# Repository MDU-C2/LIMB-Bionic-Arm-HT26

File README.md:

# AURORA

AURORA is a student project at [Mälardalen University](https://www.mdu.se/)
with the aim of developing a bionic arm for the rehabilitation of stroke
survivors. The project continues the work started in LIMB. This repository
contains the sensor firmware, recording tools, arm simulation and movement
training code.

## Platforms used

The current setup uses an ESP32-C3-Zero to read EMG and two LSM6DSO32 IMUs,
an OAK-D camera to track arm movement, and a PC to run the app and PyBullet
simulation. The ESP32 sends sensor data over Bluetooth Low Energy. The camera
connects to the PC by USB.

## Running the program

On Windows, run `Setup.bat` for the first setup, then use `Start.bat` to open
the app offline. Setup installs all app packages, checks the pose models and builds
firmware; it needs internet. See the
[setup notes](scripts/README.md) for direct launching and the macOS/Linux scripts.

Follow the [workflow guide](docs/workflow-guide.md) to connect and inspect,
prepare/calibrate, record or control, then review, process and export.
Advanced Tools contains optional training, DMP/manual joints, diagnostics and firmware.
See [architecture](docs/architecture.md) for code ownership and development conventions.

## Before recording

For the Grove EMG Detector cable with white wires and red, black and white snap heads:

| Lead | Electrode placement for grip |
| --- | --- |
| Red | Reference on a bony area near the elbow, away from the measured muscle. |
| Black | Palm-facing forearm, over the muscle that firms when making a fist. |
| White | Same muscle, a few centimetres towards the wrist from the black electrode. |

Keep black and white in line along the muscle without overlapping the pads.
Use clean, dry skin. These colours apply to this cable; see
[Seeed's placement and cable diagrams](https://wiki.seeedstudio.com/Grove-EMG_Detector/#hardware-installation).
Use battery power and BLE with USB and chargers disconnected while wearing electrodes.

In **Record**, connect camera + BLE and run **Calibrate subject** before the first
trial. This includes IMU zeroing, mounting movements and EMG rest/grip calibration.
See the [recording guide](docs/recording-guide.md#before-the-first-trial) for the
still pose and when to repeat calibration.

## Structure of repository

The main folders are:

- [`scripts/`](scripts/README.md): setup and sensor checks.
- [`src/aurora/gui/`](src/aurora/gui/README.md): the desktop app.
- [`src/aurora/sensors/`](src/aurora/sensors/README.md): sensor input, camera tracking and fusion.
- [`src/aurora/recording/`](src/aurora/recording/README.md): sensor and camera recording, grip trials and EMG processing.
- [`src/aurora/simulation/`](src/aurora/simulation/README.md): the arm simulation and playback.
- [`src/aurora/ml/`](src/aurora/ml/README.md): movement profiles and EMG classifiers.
- [`firmware/`](firmware/README.md): programs running on the ESP32-C3.
- [`data/`](data/README.md): inherited movement recordings, kept separately.
- [`docs/`](docs/README.md): setup, recording and simulation guides.
- [`tests/`](tests/README.md): software checks.

Bundled models are in `artifacts/models/`. New recordings, training runs and
generated files go in `outputs/`, which is ignored by Git.

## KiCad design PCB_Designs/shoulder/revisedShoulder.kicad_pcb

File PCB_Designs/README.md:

# PCB Designs – AURORA HT26

## Overview

This directory contains the PCB designs developed and used in the AURORA project. The boards are designed to support the robotic arm's motor control, sensor acquisition, and communication systems.

Each PCB project contains the necessary design and manufacturing files, including:

- **Schematic** – Electrical circuit design.
- **PCB Layout** – Physical component placement and routing.
- **Footprint Library** – Custom component footprints.
- **BOM (Bill of Materials)** – List of required components.
- **Gerber & Drill Files** – Files required for PCB manufacturing.

The designs are developed using **KiCad 10** and **National Instrument Multisim/Ultiboard**.

---

## PCB Modules

### 1. Biceps_Module

This PCB controls the motors responsible for movement of the biceps/lower arm using X and Y control inputs.
The module communicates with the other robotic arm controllers through the CAN bus.
- **CAN Node:** 2 of 4
- **CAN Position:** Between Shoulder (Node 1) and Hand_Motor (Node 3)
- **CAN Termination:** Not required

### 2. CAN_Transceiver

This PCB is a custom CAN transceiver board designed to enable CAN communication between the Jetson AGX Orin and the robotic arm's motor controllers.
The design is based on the [Waveshare SN65HVD230 CAN Board](https://www.waveshare.com/sn65hvd230-can-board.htm).
To reduce dependency on external component delivery times, the project group developed a custom version that could be manufactured and assembled in-house.
The same PCB design can be used throughout the CAN network.

**Important – CAN Bus Termination**
A 120 Ω termination resistor must only be installed at the two physical ends of the CAN bus.
| CAN Transceiver Location | 120 Ω Resistor |
|---|---|
| Jetson AGX Orin → Shoulder (bus start) | Installed |
| Shoulder | Not Installed |
| Biceps_Module | Not installed |
| Hand_Motor | Not installed |
| Hand_Pressure (bus end) | Installed |

Incorrect termination may lead to signal reflections, communication errors, and unstable CAN operation.

### 3. Hand_Motor

This PCB controls the motors responsible for hand movement.
It receives control commands through the CAN bus and operates as the third node in the robotic arm's communication network.
- **CAN Node:** 3 of 4
- **CAN Position:** Between Biceps_Module and Hand_Pressure
- **CAN Termination:** Not required

### 4. Hand_Pressure

This PCB is responsible for acquiring pressure measurements from the robotic hand during object grasping.
The collected sensor data can be used to monitor contact pressure and support grip control.
- **CAN Node:** 4 of 4
- **CAN Position:** Final node on the CAN bus
- **CAN Termination:** Required (120 Ω)
The CAN transceiver connected to this module must have its termination resistor installed.

### 5. Human_Sensor

This PCB is designed for the acquisition, amplification, and filtering of electromyography (EMG) signals.
The analog signal-conditioning circuit amplifies the small electrical signals generated by muscle activity and filters unwanted noise before the signals are acquired by the microcontroller.

The intended output characteristics are:
- **Resting state: Approximately 1.5 V DC output.
- **Signal noise: Low peak-to-peak voltage during rest.
- **Muscle activation: Changes in the output signal corresponding to measured muscle activity.

The PCB also provides mounting positions for:
- **ESP32-C3 – Microcontroller for data acquisition and communication.
- **IMU – Inertial Measurement Unit for motion sensing.

The Human_Sensor PCB is part of the user-worn sensing system and is separate from the robotic arm's CAN motor-controller network.

CAN Bus Architecture
The robotic arm uses a shared CAN bus connecting the Jetson AGX Orin to four ESP32-based control nodes.

Jetson AGX Orin
       |
  CAN Transceiver
   [120 Ω ON]
       |
       |
 Shoulder Module
     Node 1
       |
       |
 Biceps_Module
     Node 2
       |
       |
   Hand_Motor
     Node 3
       |
       |
  Hand_Pressure
     Node 4
   [120 Ω ON]

Note: The termination resistors must be located at the two physical endpoints of the CAN bus. The diagram represents the intended bus topology; exact transceiver placement depends on the final wiring arrangement.

Notes
The custom CAN transceiver PCB is designed for reuse across multiple robotic arm modules.
CAN termination must be configured according to the physical bus topology.
Custom KiCad footprints are stored in the corresponding project libraries to simplify project sharing.
PCB designs should be verified before manufacturing or assembly.

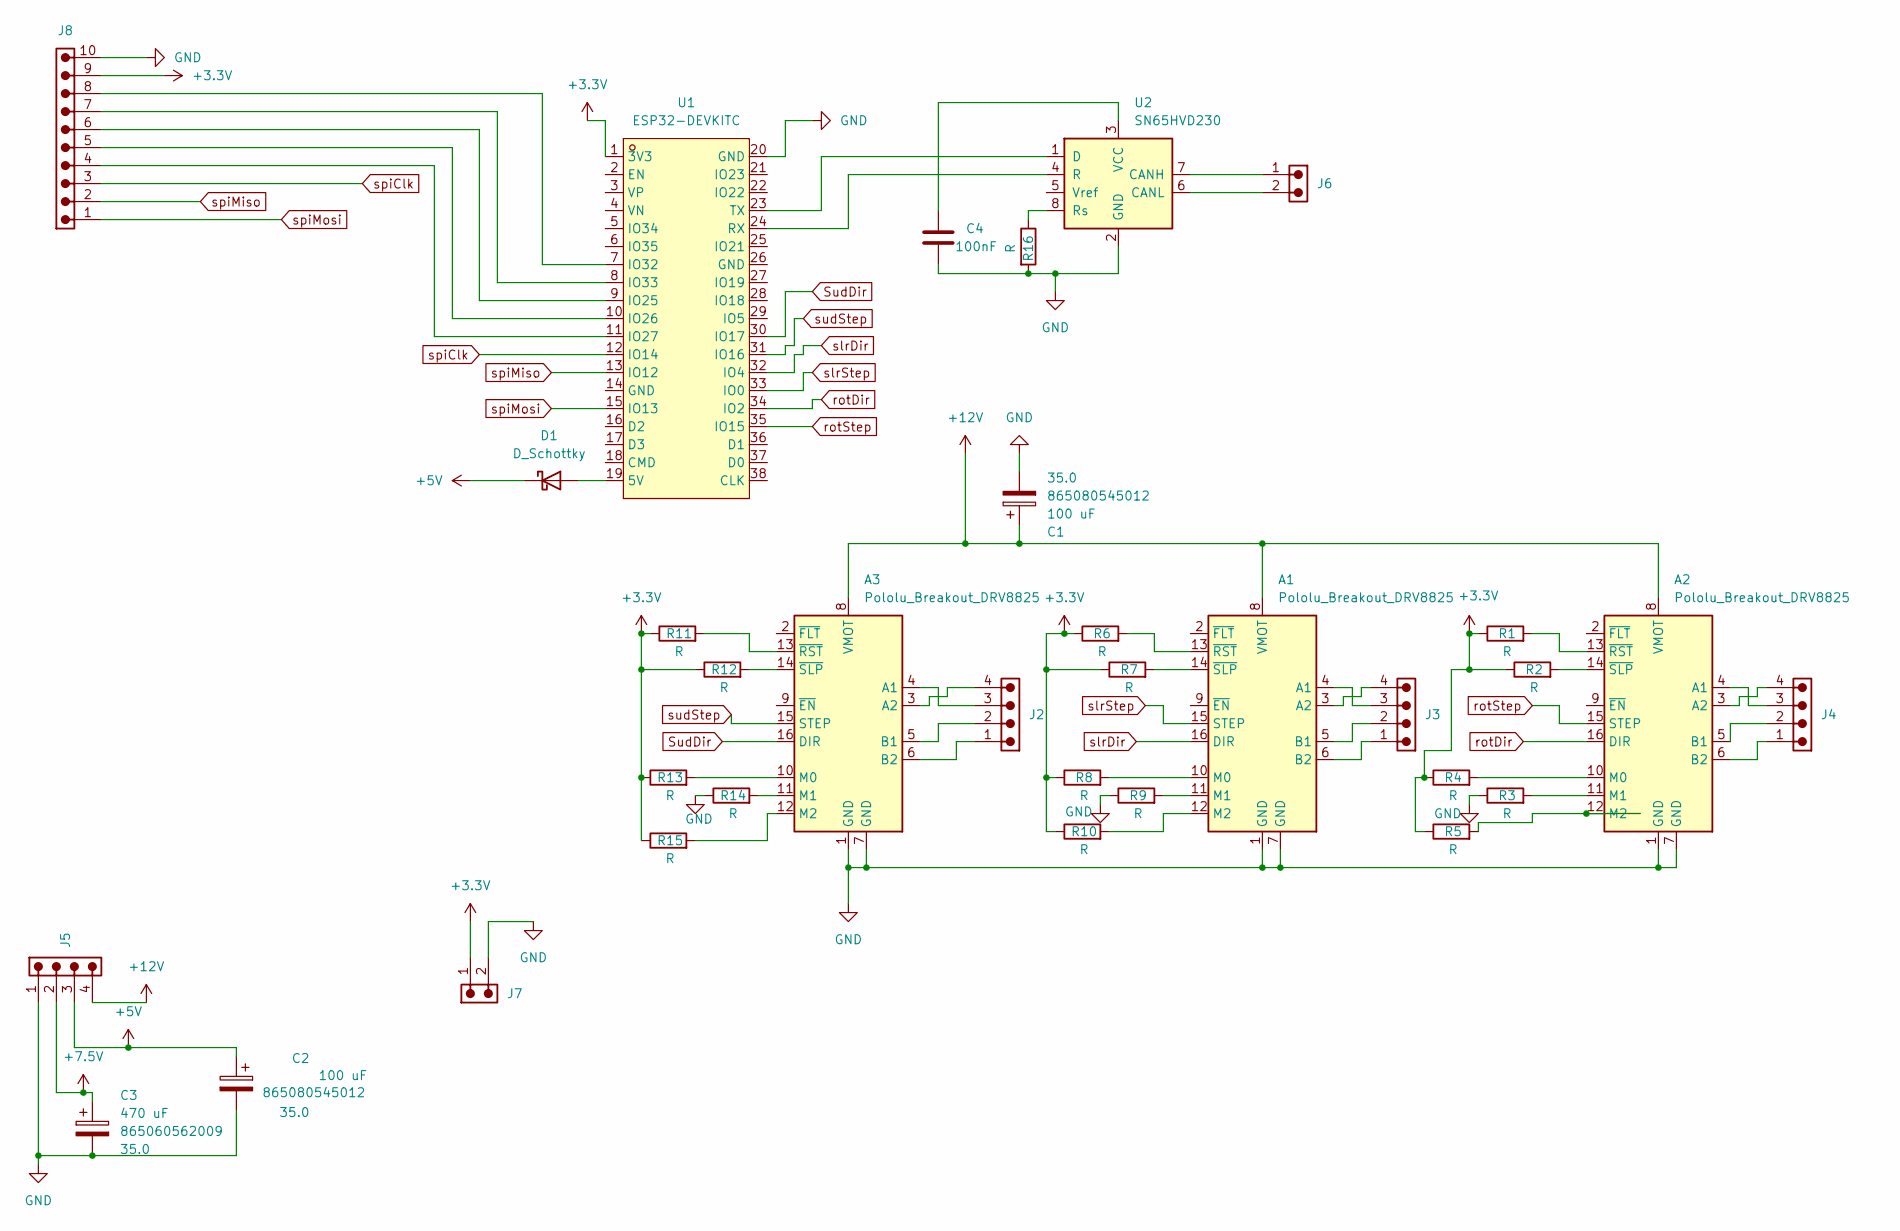
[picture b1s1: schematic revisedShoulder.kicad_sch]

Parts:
A1, A2, A3: Pololu_Breakout_DRV8825; Pololu_Breakout-16_15.2x20.3mm
C1, C2: 100 uF; CP_Wurth_WCAP-ASLI-D6.3L7.7; Voltage 35.0; Part Number 865080545012
C3: 470 uF; CP_Wurth_WCAP-ASLL-D12.5L14; Voltage 35.0; Part Number 865060562009
C4: 100nF; C_0805_2012Metric_Pad1.18x1.45mm_HandSolder
D1: D_Schottky; D_SMA_Handsoldering
J2, J3, J4: 61900411121; J_Wurth_WR-WTB_61900411121; Working Voltage (V (AC)) 250
J5: 68800411622; J_Wurth_WR-WTB_68800411622; Working Voltage (V (AC)) 250
J6, J7: 68800211622; J_Wurth_WR-WTB_68800211622; Working Voltage (V (AC)) 250
J8: 68801011622; J_Wurth_WR-WTB_68801011622; Working Voltage (V (AC)) 250
R1, R2, R3, R4, R5, R6, R7, R8, R9, R10, R11, R12, R13, R14, R15, R16: R; R_0805_2012Metric_Pad1.20x1.40mm_HandSolder
U1: ESP32-DEVKITC; BULETM-SMD_ESP32-DEVKITC; MPN ESP32-DevKitC; LCSC Part C571180
U2: SN65HVD230; SOIC-8_3.9x4.9mm_P1.27mm

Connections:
+3.3V: J7.1, J8.9, R1.1, R2.1, R4.1, R5.1, R6.1, R7.1, R8.1, R10.1, R11.1, R12.1, R13.1, R15.1, U1.1 (3V3)
+5V: C2.1, D1.1 (K), J5.3
+7.5V: C3.1, J5.2
+12V: A1.8 (VMOT), A2.8 (VMOT), A3.8 (VMOT), C1.1, J5.4
GND: A1.1 (GND), A1.7 (GND), A2.1 (GND), A2.7 (GND), A3.1 (GND), A3.7 (GND), C1.2, C2.2, C3.2, C4.2, J5.1, J7.2, J8.10, R3.1, R9.1, R14.1, R16.2, U1.20 (GND), U2.2 (GND)
unnamed: A1.4 (A1), J3.3
unnamed: A1.3 (A2), J3.4
unnamed: A1.5 (B1), J3.2
unnamed: A1.6 (B2), J3.1
unnamed: A1.10 (M0), R8.2
unnamed: A1.11 (M1), R9.2
unnamed: A1.12 (M2), R10.2
unnamed: A1.13 (~RST), R6.2
unnamed: A1.14 (~SLP), R7.2
unnamed: A2.4 (A1), J4.3
unnamed: A2.3 (A2), J4.4
unnamed: A2.5 (B1), J4.2
unnamed: A2.6 (B2), J4.1
unnamed: A2.10 (M0), R4.2
unnamed: A2.11 (M1), R3.2
unnamed: A2.12 (M2), R5.2
unnamed: A2.13 (~RST), R1.2
unnamed: A2.14 (~SLP), R2.2
unnamed: A3.4 (A1), J2.3
unnamed: A3.3 (A2), J2.4
unnamed: A3.5 (B1), J2.2
unnamed: A3.6 (B2), J2.1
unnamed: A3.10 (M0), R13.2
unnamed: A3.11 (M1), R14.2
unnamed: A3.12 (M2), R15.2
unnamed: A3.13 (~RST), R11.2
unnamed: A3.14 (~SLP), R12.2
unnamed: D1.2 (A), U1.19 (5V)
unnamed: J8.6, U1.9 (IO25)
unnamed: J8.5, U1.10 (IO26)
unnamed: J8.4, U1.11 (IO27)
unnamed: J8.8, U1.7 (IO32)
unnamed: J8.7, U1.8 (IO33)
unnamed: U1.24 (RX), U2.4 (R)
unnamed: U1.23 (TX), U2.1 (D)
unnamed: J6.1, U2.7 (CANH)
unnamed: J6.2, U2.6 (CANL)
unnamed: R16.1, U2.8 (Rs)
unnamed: C4.1, U2.3 (VCC)
SudDir: A3.16 (DIR), U1.30 (IO17)
rotDir: A2.16 (DIR), U1.34 (IO2)
rotStep: A2.15 (STEP), U1.35 (IO15)
slrDir: A1.16 (DIR), U1.32 (IO4)
slrStep: A1.15 (STEP), U1.33 (IO0)
spiClk: J8.3, U1.12 (IO14)
spiMiso: J8.2, U1.13 (IO12)
spiMosi: J8.1, U1.15 (IO13)
sudStep: A3.15 (STEP), U1.31 (IO16)

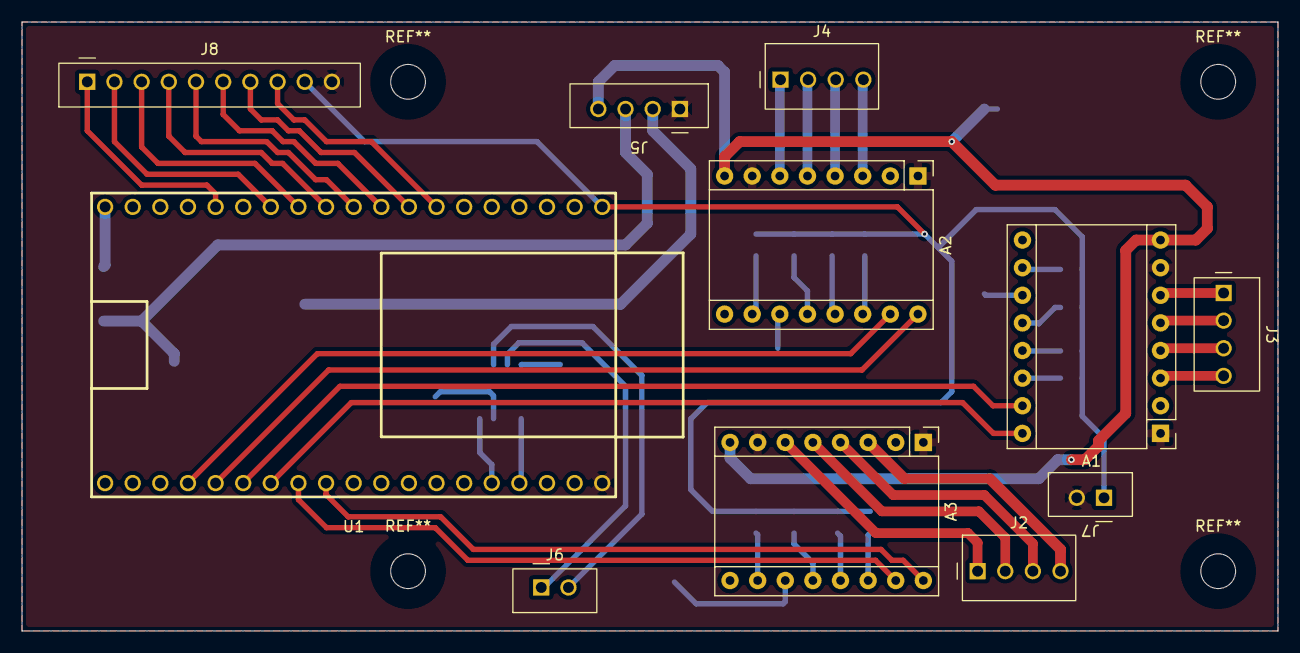
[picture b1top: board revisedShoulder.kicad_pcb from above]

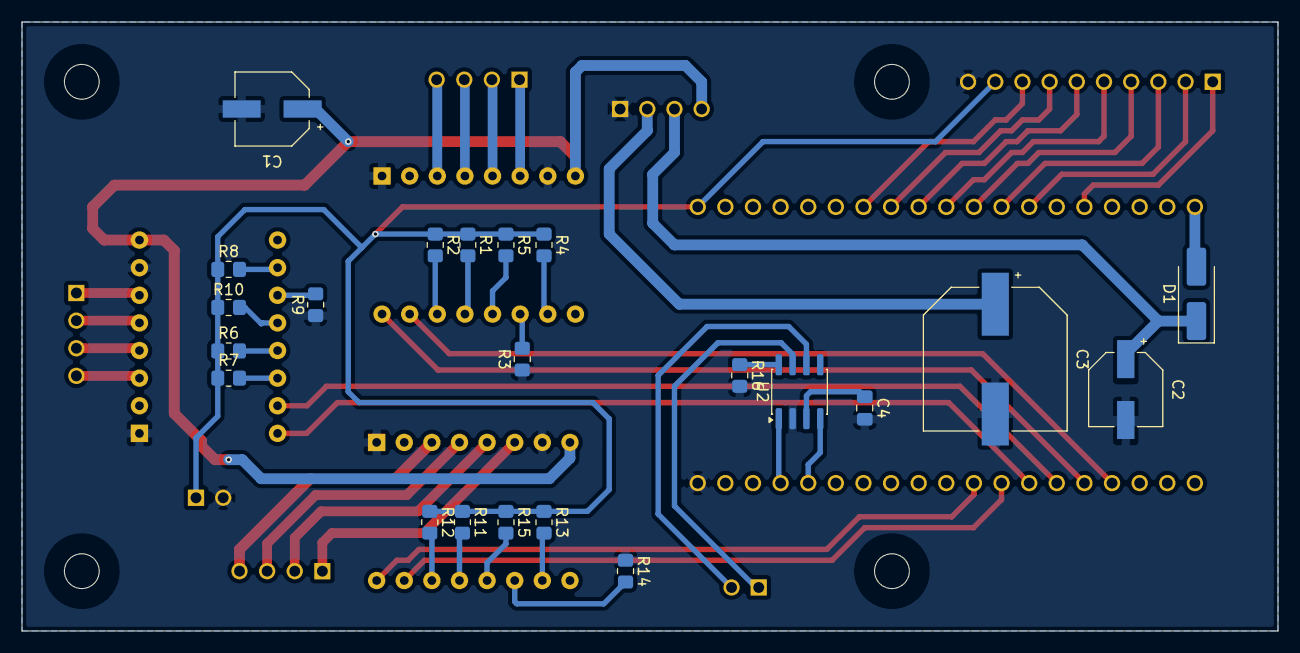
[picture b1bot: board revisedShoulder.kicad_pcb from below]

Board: 2 copper layers, 115.5 x 56.0 mm, 33 parts (22 on the bottom side), 53 nets.

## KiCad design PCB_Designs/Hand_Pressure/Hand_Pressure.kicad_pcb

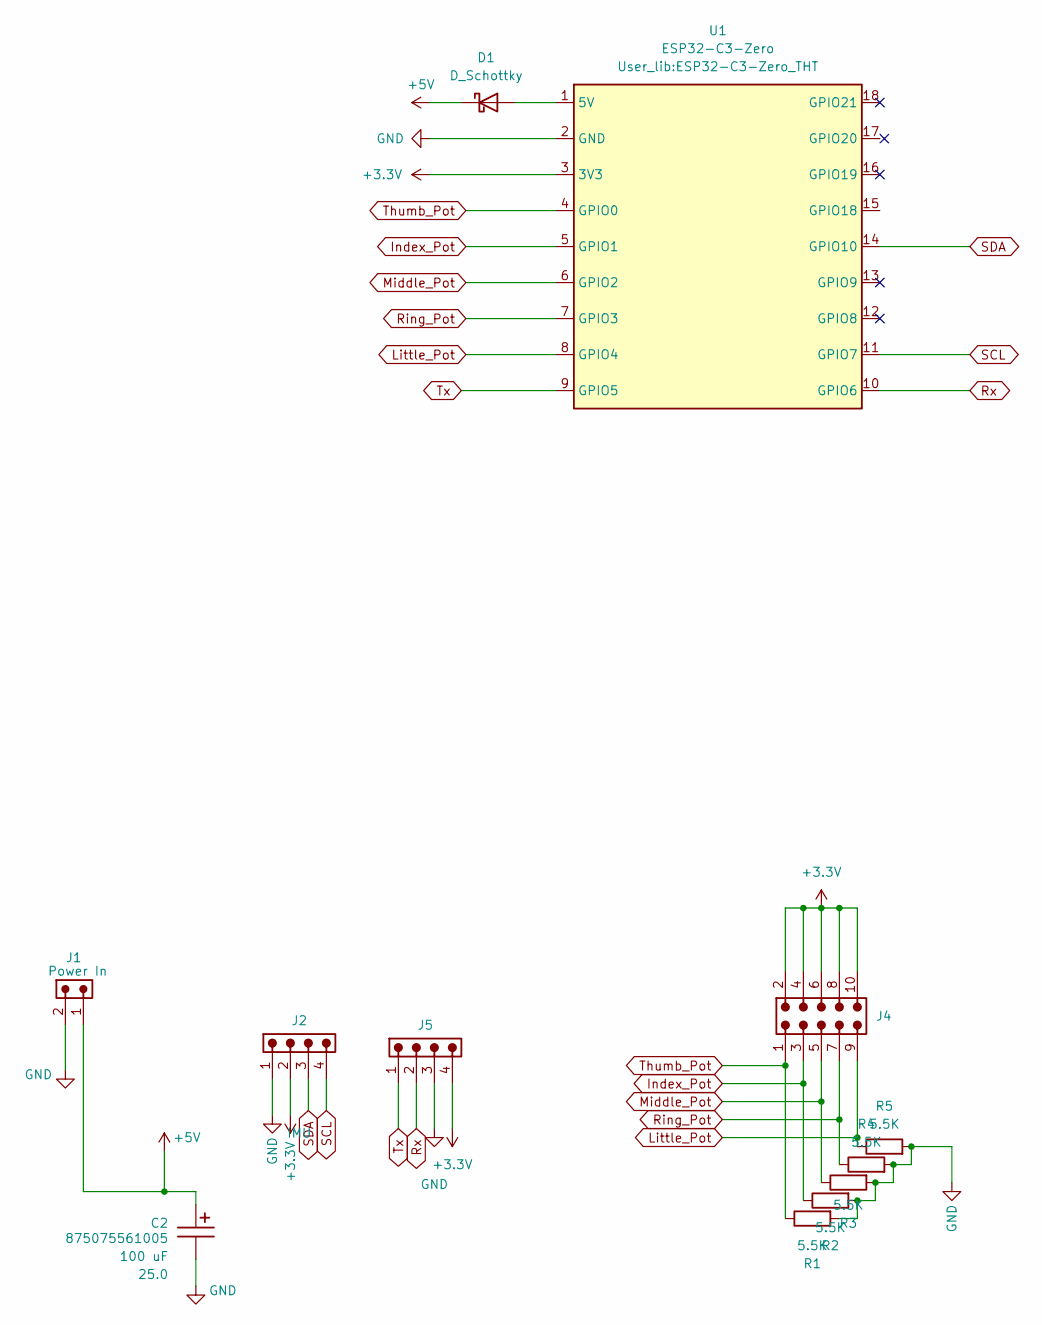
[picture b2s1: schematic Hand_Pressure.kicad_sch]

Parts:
C2: 100 uF; CP_Wurth_WCAP-ASLL-D6.3L5.5; Voltage 25.0; Part Number 875075561005
D1: D_Schottky; D_SMA
J1: Power In; J_Wurth_WR-NPC2_626002110201; Part Number 626002110201
J2: IMU; J_Wurth_WR-WTB_68800411622; Working Voltage (V (AC)) 250
J4: 61301021121; J_Wurth_WR-PHD_61301021121
J5: IMU; J_Wurth_WR-PHD_613004143121; Working Voltage (V (AC)) 250
R1, R2, R3, R4, R5: 5.5K; R_0805_2012Metric
U1: ESP32-C3-Zero; ESP32-C3-Zero_THT

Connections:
+3.3V: J2.2, J4.2, J4.4, J4.6, J4.8, J4.10, J5.4, U1.3 (3V3)
+5V: C2.1, D1.1 (K), J1.1
GND: C2.2, J1.2, J2.1, J5.3, R1.2, R2.2, R3.2, R4.2, R5.2, U1.2 (GND)
Index_Pot: J4.3, R2.1, U1.5 (GPIO1)
Little_Pot: J4.9, R5.1, U1.8 (GPIO4)
Middle_Pot: J4.5, R3.1, U1.6 (GPIO2)
unnamed: D1.2 (A), U1.1 (5V)
Ring_Pot: J4.7, R4.1, U1.7 (GPIO3)
Rx: J5.2, U1.10 (GPIO6)
SCL: J2.4, U1.11 (GPIO7)
SDA: J2.3, U1.14 (GPIO10)
Thumb_Pot: J4.1, R1.1, U1.4 (GPIO0)
Tx: J5.1, U1.9 (GPIO5)

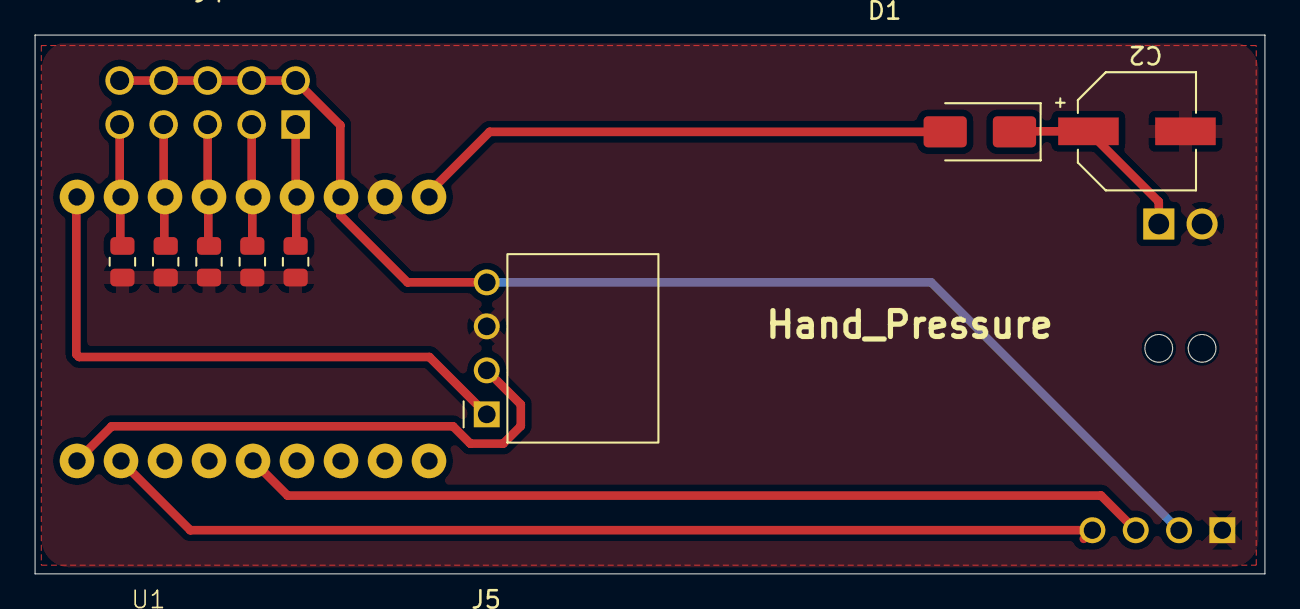
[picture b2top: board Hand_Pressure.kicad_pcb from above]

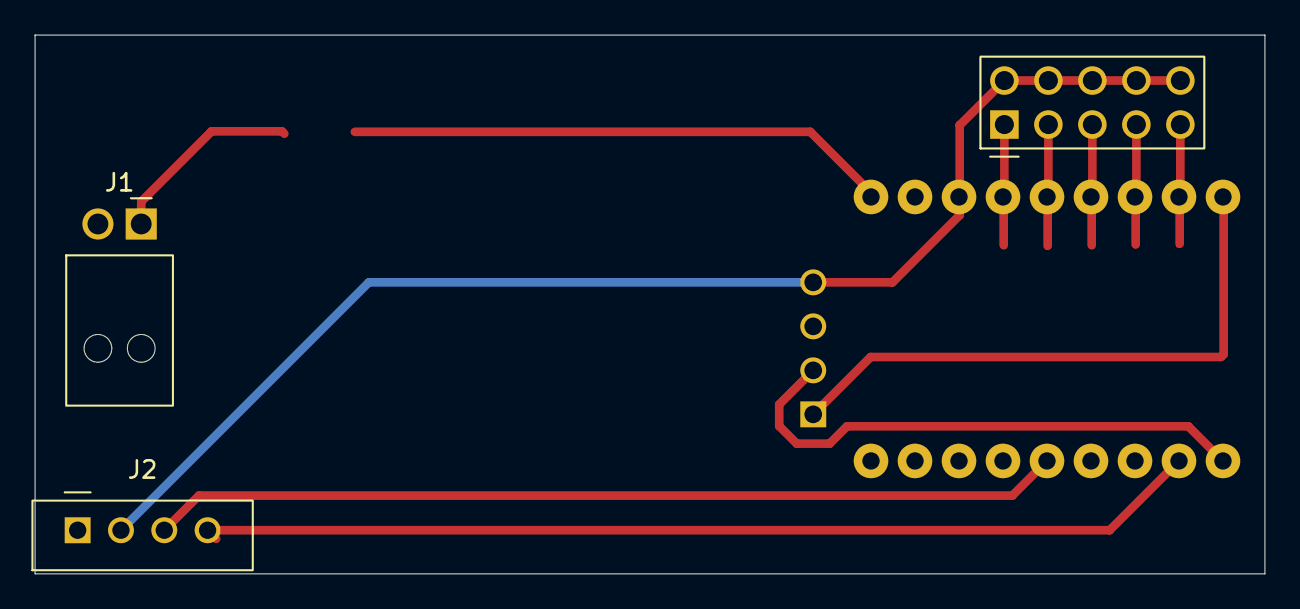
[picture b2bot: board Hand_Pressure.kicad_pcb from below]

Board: 2 copper layers, 71.0 x 31.1 mm, 12 parts (3 on the bottom side), 13 nets.

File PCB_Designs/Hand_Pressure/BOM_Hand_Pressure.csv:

Reference;Qty;Value;Footprint;Datasheet
C2;1;100 uF;Capacitor_SMD_Wurth:CP_Wurth_WCAP-ASLL-D6.3L5.5;https://www.we-online.com/catalog/datasheet/875075561005.pdf?ki
D1;1;D_Schottky;Diode_SMD:D_SMA;https://docs.rs-online.com/28a6/0900766b80de2cd0.pdf
J1;1;Power In;User_lib:J_Wurth_WR-NPC2_626002110201;https://www.we-online.com/catalog/datasheet/626002110201.pdf?ki
J2;1;IMU;User_lib:J_Wurth_WR-WTB_68800411622;https://www.we-online.com/en/components/products/datasheet/6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
J4;1;61301021121;User_lib:J_Wurth_WR-PHD_61301021121;https://www.we-online.com/en/components/products/datasheet/6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
J5;1;IMU;Connector_THT_Wurth:J_Wurth_WR-PHD_613004143121;https://www.we-online.com/components/products/datasheet/6130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
R1,R2,R3,R4,R5;5;5.5K;Resistor_SMD:R_0805_2012Metric;
U1;1;ESP32-C3-Zero;User_lib:ESP32-C3-Zero_THT;https://www.waveshare.com/wiki/ESP32-C3-Zero#Resource
U1;2;ESP32 Connector;9-pin Connectors for ESP32-C3 ;https://www.we-online.com/en/components/products/BTB_WR_PHD_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

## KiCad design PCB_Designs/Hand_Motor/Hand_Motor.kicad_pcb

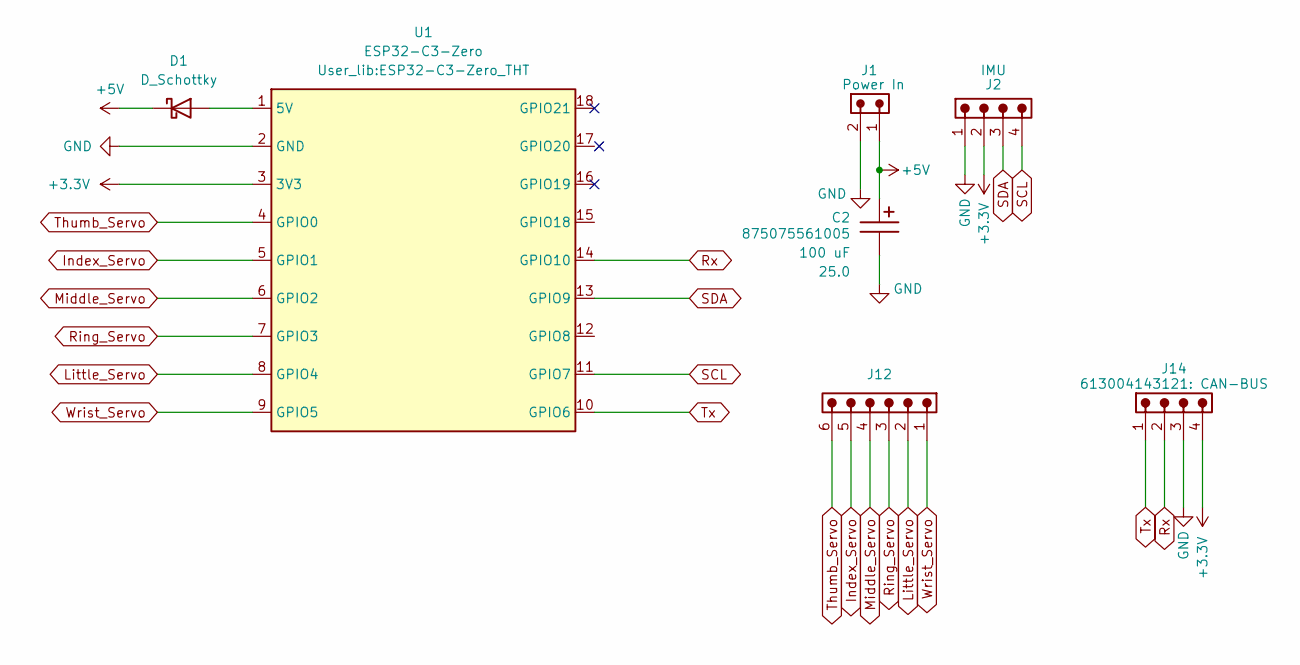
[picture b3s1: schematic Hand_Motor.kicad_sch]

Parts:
C2: 100 uF; CP_Wurth_WCAP-ASLL-D6.3L5.5; Voltage 25.0; Part Number 875075561005
D1: D_Schottky; D_SMA
J1: Power In; J_Wurth_WR-NPC2_626002110201; Part Number 626002110201
J2: IMU; J_Wurth_WR-WTB_68800411622; Working Voltage (V (AC)) 250
J12: 68800611722; J_Wurth_WR-WTB_68800611722; Working Voltage (V (AC)) 250
J14: 613004143121: CAN-BUS; PinHeader_1x04_P2.54mm_Vertical; Working Voltage (V (AC)) 250
U1: ESP32-C3-Zero; ESP32-C3-Zero_THT

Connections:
+3.3V: J2.2, J14.4, U1.3 (3V3); also elsewhere on the board
+5V: C2.1, D1.1 (K), J1.1
GND: C2.2, J1.2, J2.1, J14.3, U1.2 (GND); also elsewhere on the board
Index_Servo: J12.5, U1.5 (GPIO1)
Little_Servo: J12.2, U1.8 (GPIO4)
Middle_Servo: J12.4, U1.6 (GPIO2)
unnamed: D1.2 (A), U1.1 (5V)
Ring_Servo: J12.3, U1.7 (GPIO3)
Rx: J14.2, U1.14 (GPIO10)
SCL: J2.4, U1.11 (GPIO7)
SDA: J2.3, U1.13 (GPIO9)
Thumb_Servo: J12.6, U1.4 (GPIO0)
Tx: J14.1, U1.10 (GPIO6)
Wrist_Servo: J12.1, U1.9 (GPIO5)

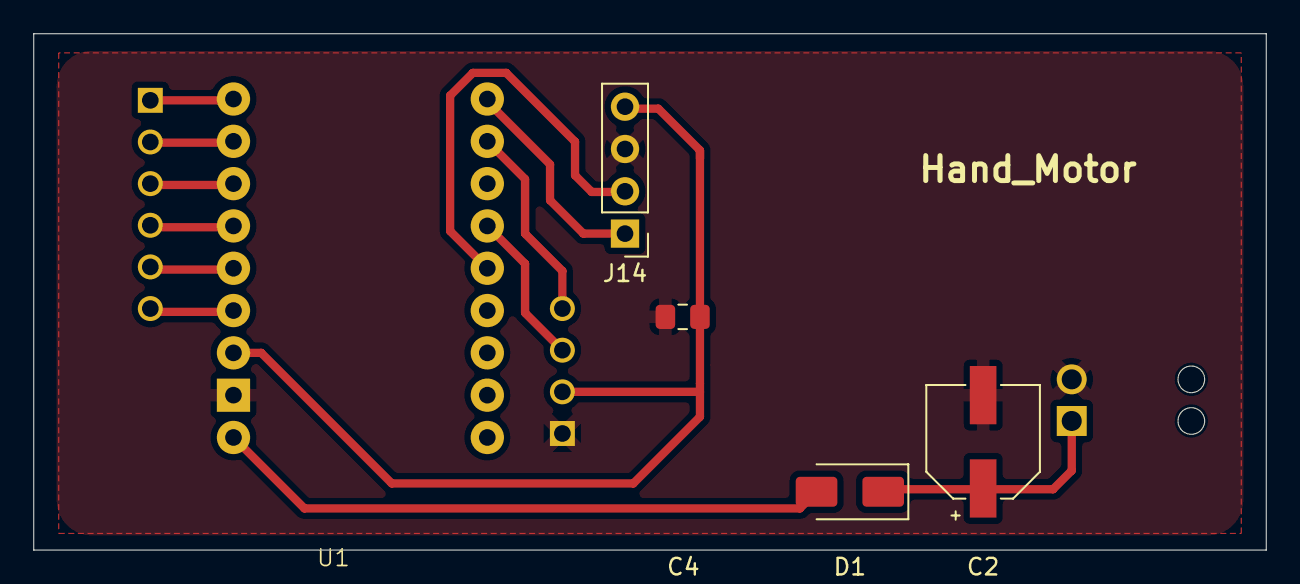
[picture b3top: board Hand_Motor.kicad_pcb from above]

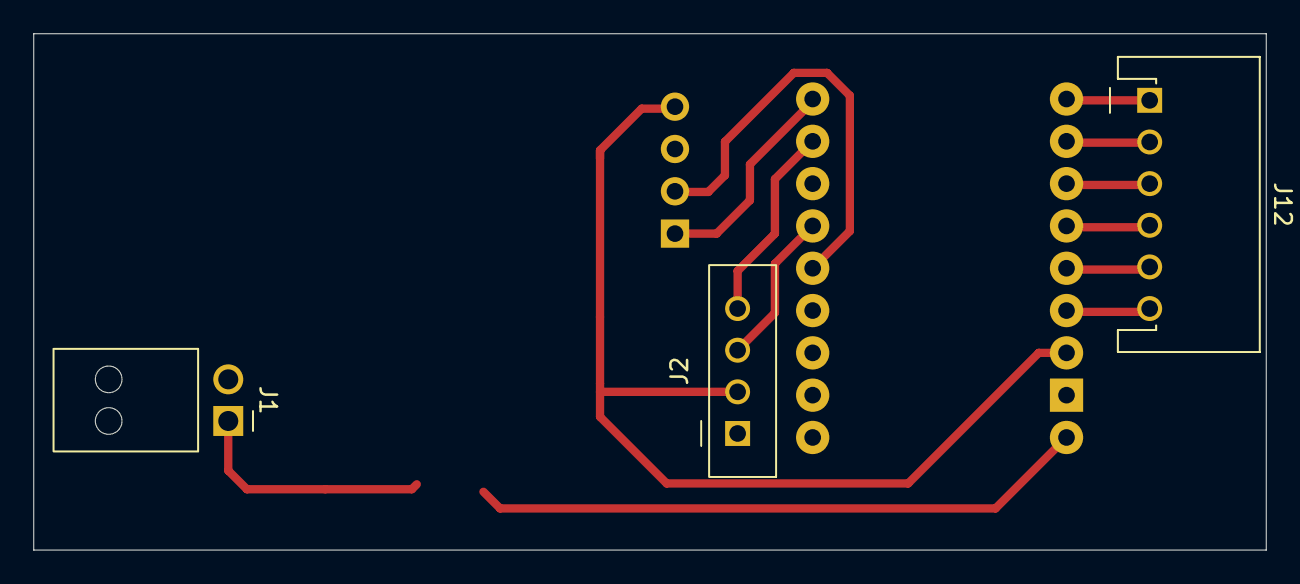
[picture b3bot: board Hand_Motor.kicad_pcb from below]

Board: 2 copper layers, 74.0 x 31.0 mm, 8 parts (4 on the bottom side), 14 nets.

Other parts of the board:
C4: 100nF; C_0805_2012Metric_Pad1.18x1.45mm_HandSolder

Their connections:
+3.3V: C4.2; also elsewhere on the board
GND: C4.1; also elsewhere on the board

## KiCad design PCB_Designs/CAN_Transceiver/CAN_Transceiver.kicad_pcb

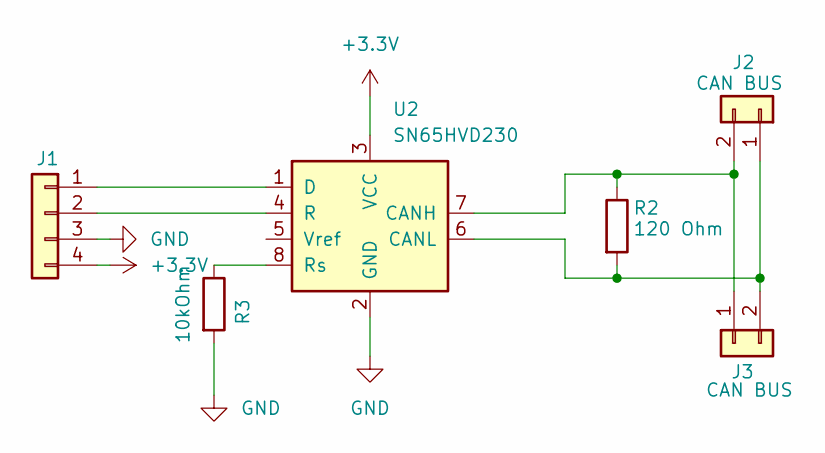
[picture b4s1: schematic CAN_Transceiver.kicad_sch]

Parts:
J1: Conn_01x04; PinHeader_1x04_P2.54mm_Horizontal
J2, J3: CAN BUS; J_Wurth_WR-WTB_68800211722
R2: 120 Ohm; R_0603_1608Metric_Pad0.98x0.95mm_HandSolder
R3: 10kOhm; R_0603_1608Metric_Pad0.98x0.95mm_HandSolder
U2: SN65HVD230; SOIC-8_3.9x4.9mm_P1.27mm

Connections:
+3.3V: J1.4, U2.3 (VCC)
GND: J1.3, R3.2, U2.2 (GND)
unnamed: J1.1, U2.1 (D)
unnamed: J1.2, U2.4 (R)
unnamed: J2.1, J3.2, R2.2, U2.6 (CANL)
unnamed: J2.2, J3.1, R2.1, U2.7 (CANH)
unnamed: R3.1, U2.8 (Rs)

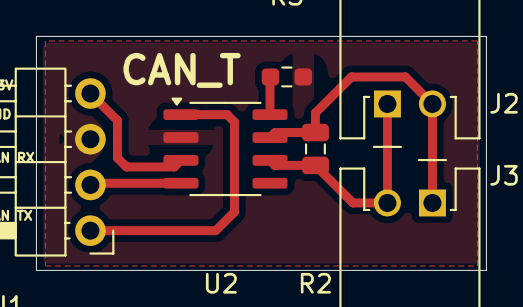
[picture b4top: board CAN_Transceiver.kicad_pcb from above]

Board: 2 copper layers, 25.0 x 13.0 mm, 6 parts (0 on the bottom side), 7 nets.

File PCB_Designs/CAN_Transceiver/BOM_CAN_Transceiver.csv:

Reference;Qty;Value;Footprint;Datasheet;Comments
J1;1;Conn_01x04;Connector_PinHeader_2.54mm:PinHeader_1x04_P2.54mm_Horizontal;https://www.we-online.com/components/products/datasheet/6130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;
J2,J3;2;CAN_01x02_male;User_lib:J_Wurth_WR-WTB_68800211722;https://www.we-online.com/en/components/products/WTB_WR_WTB_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;
J2,J3;2;Conn_01x02_female;User_lib:J_Wurth_WR-WTB_688002113322;https://www.we-online.com/en/components/products/WTB_2_50_J_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;Used for cords
R2;1;120 Ohm;Resistor_SMD:R_0603_1608Metric_Pad0.98x0.95mm_HandSolder;;
R3;1;10kOhm;Resistor_SMD:R_0603_1608Metric_Pad0.98x0.95mm_HandSolder;;
U2;1;SN65HVD230;Package_SO:SOIC-8_3.9x4.9mm_P1.27mm;http://www.ti.com/lit/ds/symlink/sn65hvd230.pdf;

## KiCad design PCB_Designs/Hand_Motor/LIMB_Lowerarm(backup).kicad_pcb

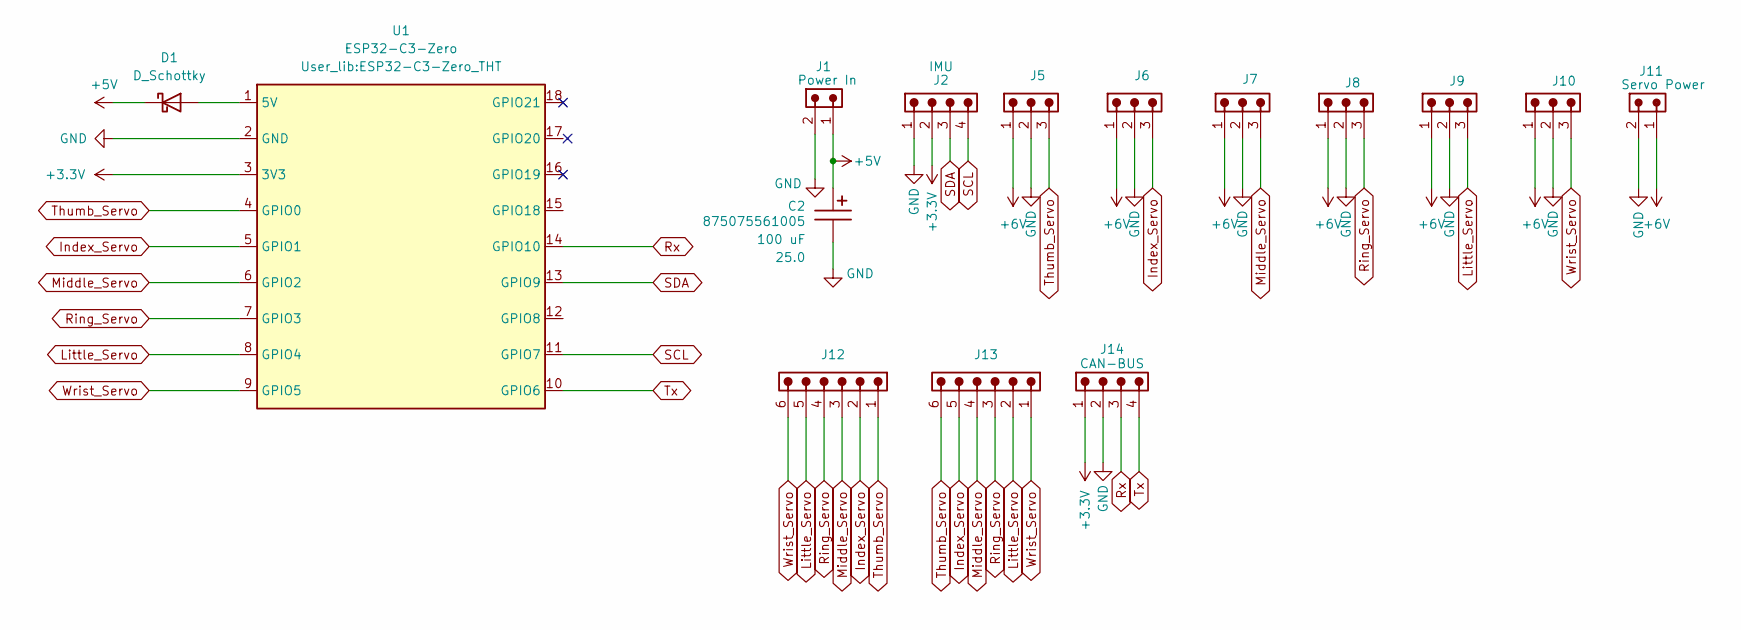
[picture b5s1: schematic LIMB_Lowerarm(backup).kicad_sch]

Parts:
C2: 100 uF; CP_Wurth_WCAP-ASLL-D6.3L5.5; Voltage 25.0; Part Number 875075561005
D1: D_Schottky; D_SMA
J1: Power In; J_Wurth_WR-NPC2_626002110201; Part Number 626002110201
J2: IMU; J_Wurth_WR-WTB_68800411622; Working Voltage (V (AC)) 250
J5, J6, J7, J8, J9, J10: 68800311622; J_Wurth_WR-WTB_68800311622; Working Voltage (V (AC)) 250
J11: Servo Power; J_Wurth_WR-NPC2_626002110201; Part Number 626002110201
J12, J13: 68800611722; J_Wurth_WR-WTB_68800611722; Working Voltage (V (AC)) 250
J14: CAN-BUS; J_Wurth_WR-WTB_68800411622; Working Voltage (V (AC)) 250
U1: ESP32-C3-Zero; ESP32-C3-Zero_THT

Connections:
+3.3V: J2.2, J14.1, U1.3 (3V3); also elsewhere on the board
+5V: C2.1, D1.1 (K), J1.1
+6V: J5.1, J6.1, J7.1, J8.1, J9.1, J10.1, J11.1
GND: C2.2, J1.2, J2.1, J5.2, J6.2, J7.2, J8.2, J9.2, J10.2, J11.2, J14.2, U1.2 (GND); also elsewhere on the board
Index_Servo: J6.3, J12.2, J13.5, U1.5 (GPIO1)
Little_Servo: J9.3, J12.5, J13.2, U1.8 (GPIO4)
Middle_Servo: J7.3, J12.3, J13.4, U1.6 (GPIO2)
unnamed: D1.2 (A), U1.1 (5V)
Ring_Servo: J8.3, J12.4, J13.3, U1.7 (GPIO3)
Rx: J14.3, U1.14 (GPIO10)
SCL: J2.4, U1.11 (GPIO7)
SDA: J2.3, U1.13 (GPIO9)
Thumb_Servo: J5.3, J12.1, J13.6, U1.4 (GPIO0)
Tx: J14.4, U1.10 (GPIO6)
Wrist_Servo: J10.3, J12.6, J13.1, U1.9 (GPIO5)

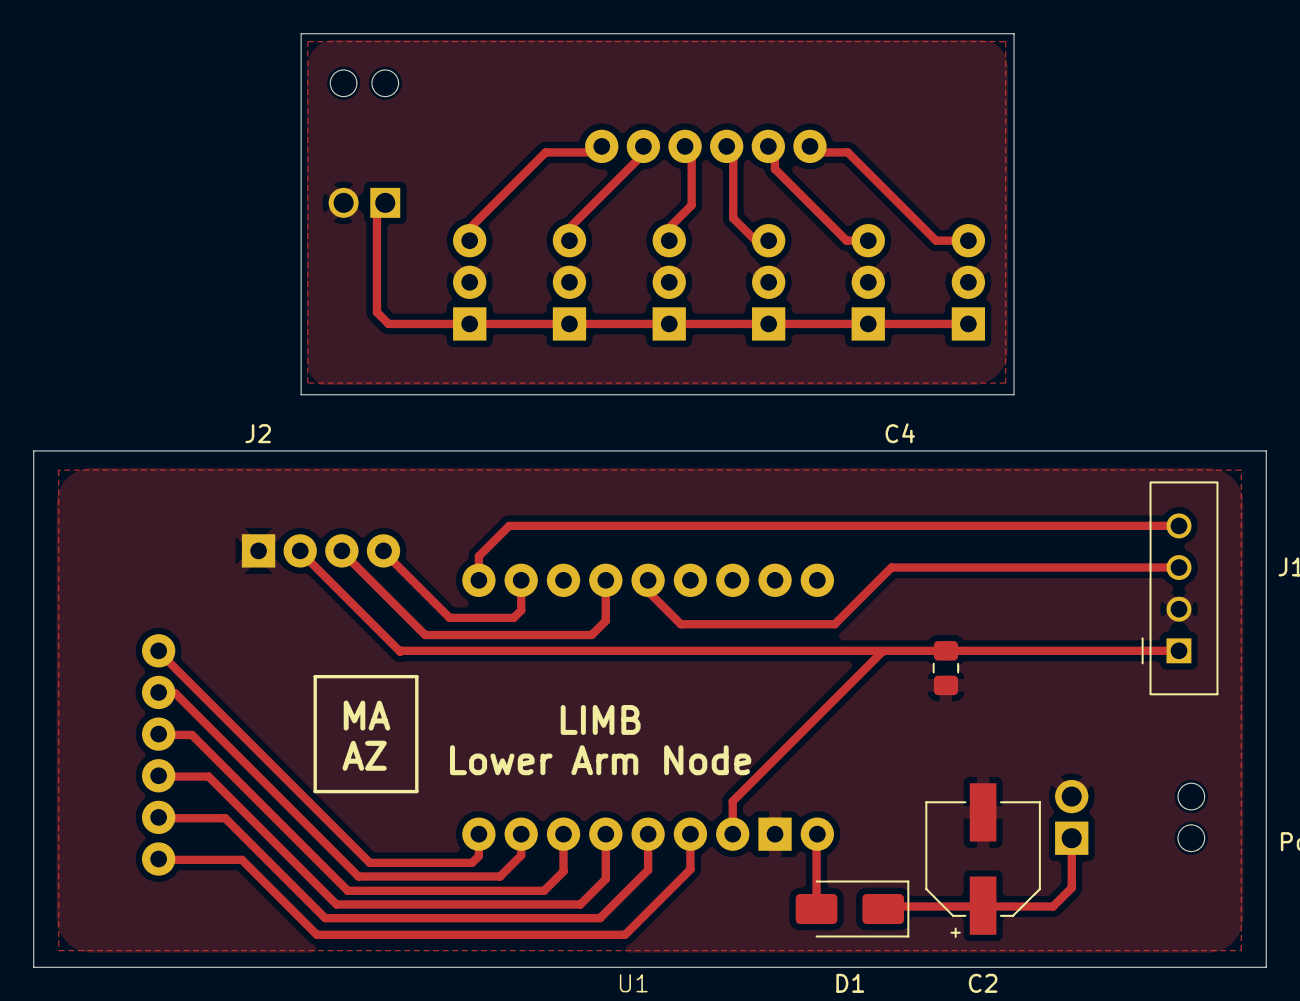
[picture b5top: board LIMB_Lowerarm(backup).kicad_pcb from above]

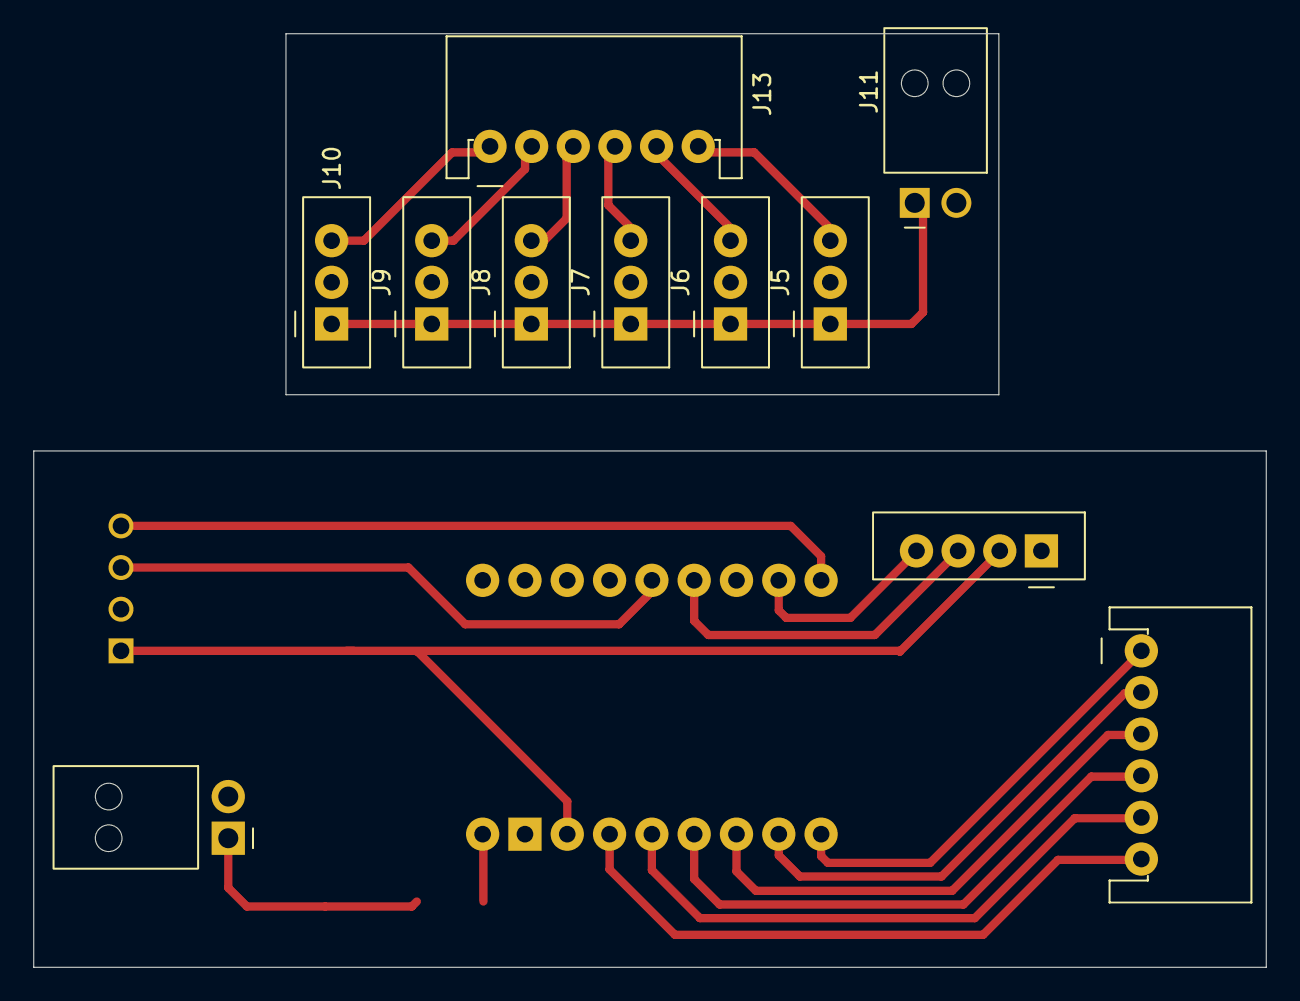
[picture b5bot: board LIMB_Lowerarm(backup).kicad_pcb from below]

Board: 2 copper layers, 74.0 x 56.0 mm, 16 parts (12 on the bottom side), 15 nets.

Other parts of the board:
C4: 100nF; C_0805_2012Metric_Pad1.18x1.45mm_HandSolder

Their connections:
+3.3V: C4.2; also elsewhere on the board
GND: C4.1; also elsewhere on the board
